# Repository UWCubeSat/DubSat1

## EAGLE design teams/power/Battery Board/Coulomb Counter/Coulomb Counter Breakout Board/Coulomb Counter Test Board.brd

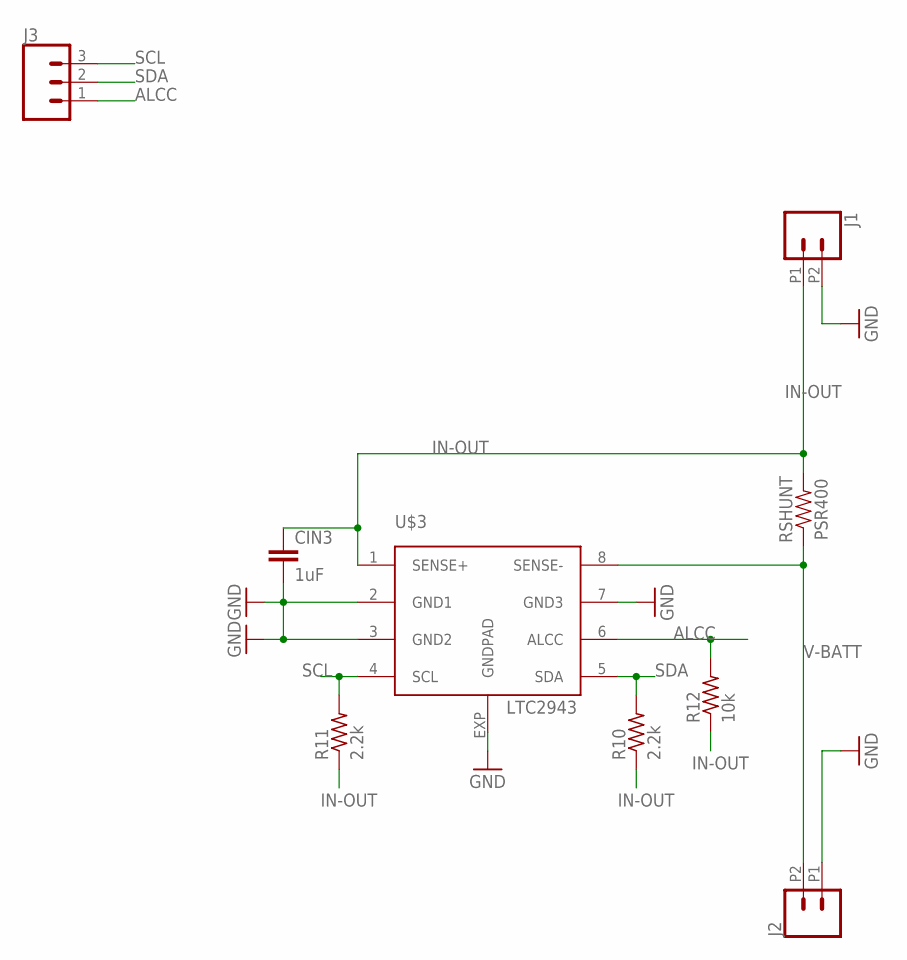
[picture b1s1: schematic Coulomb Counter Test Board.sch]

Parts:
CIN3: 1uF; 0402-CAP
J1, J2: CONN_022.54MM_SCREWTERM; 1X02_2.54_SCREWTERM
J3: CONN_03; 1X03
R10, R11: 2.2k; R0805
R12: 10k; R0805
RSHUNT: PSR400
U$3: LTC2943; DFN8(3X3)LT

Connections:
ALCC: J3.1, R12.2, U$3.6 (ALCC)
GND: CIN3.2, J1.P2 (2), J2.P1 (1), U$3.2 (GND1), U$3.3 (GND2), U$3.7 (GND3), U$3.EXP (GNDPAD)
IN-OUT: CIN3.1, J1.P1 (1), R10.1, R11.1, R12.1, RSHUNT.P$2 (2), U$3.1 (SENSE+)
SCL: J3.3, R11.2, U$3.4 (SCL)
SDA: J3.2, R10.2, U$3.5 (SDA)
V-BATT: J2.P2 (2), RSHUNT.P$1 (1), U$3.8 (SENSE-)

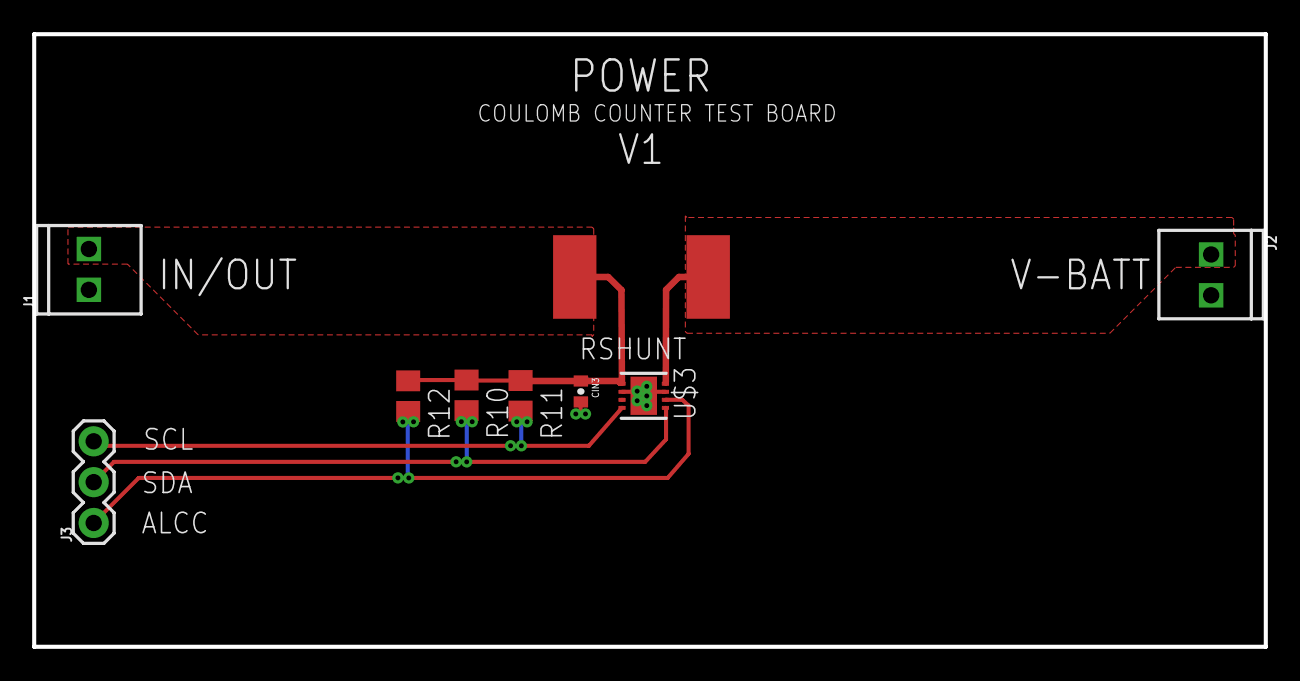
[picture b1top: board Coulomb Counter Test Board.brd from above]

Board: 2 copper layers, 76.6 x 38.1 mm, 9 parts (0 on the bottom side), 6 nets.

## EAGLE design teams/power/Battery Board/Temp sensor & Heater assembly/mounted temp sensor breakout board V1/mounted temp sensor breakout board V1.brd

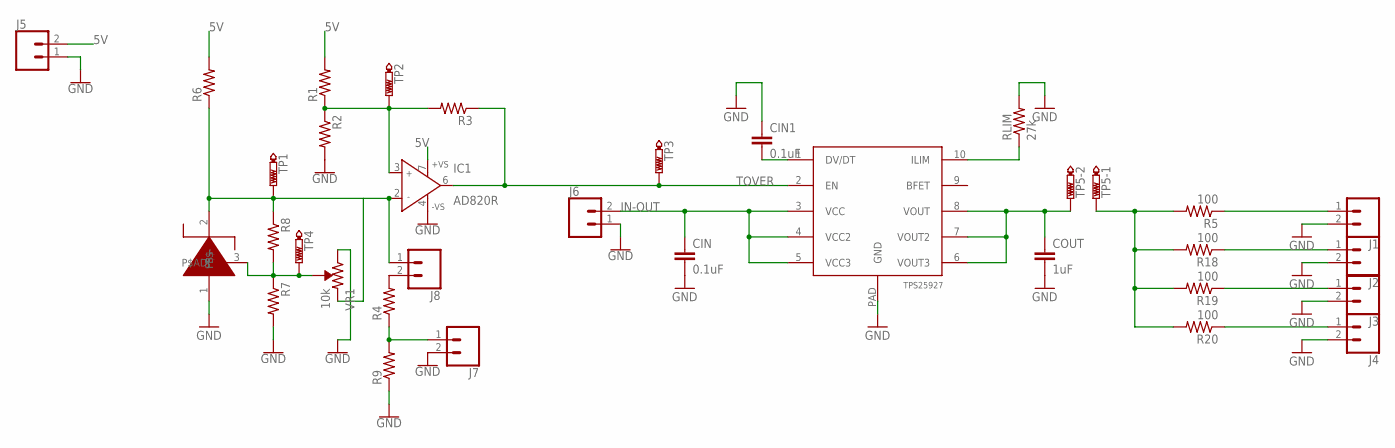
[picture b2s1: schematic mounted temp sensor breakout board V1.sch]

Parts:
CIN, CIN1: 0.1uF; C0805
COUT: 1uF; C0805
IC1: AD820R; SO8
J1, J2, J3, J4, J5, J6, J7, J8: CONN_02; 1X02
R1, R2, R3, R4, R6, R7, R8, R9: R-US_R0805; R0805
R5, R18, R19, R20: 100; R0805
RLIM: 27k; R0805
TP1, TP2, TP3, TP4: PTR1PAD1-13Y; P1-13Y
TP5: PTR2; P2-38-17
U$1: LM135Z; TO-92-3
U$5: TPS252927; VSON10
VR1: 10k; TRIMPOT-SMD-TC33X

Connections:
5V: IC1.7 (+VS), J5.2, R1.2, R6.2
GND: CIN.2, CIN1.1, COUT.2, IC1.4 (-VS), J1.2, J2.2, J3.2, J4.2, J5.1, J6.1, J7.2, R2.2, R7.2, R9.1, RLIM.2, U$1.1 (P$-), U$5.PAD (GND), VR1.1 (CW)
HEATER1: J3.1, R19.1
IN-OUT: CIN.1, J6.2, U$5.3 (VCC), U$5.4 (VCC2), U$5.5 (VCC3)
unnamed: J1.1, R5.1
unnamed: IC1.3 (IN+), R1.1, R2.1, R3.2, TP2.TP
unnamed: IC1.2 (IN-), J8.1, R6.1, R8.1, TP1.TP, U$1.2 (P$+), VR1.3 (CCW)
unnamed: R7.1, R8.2, TP4.TP, U$1.3 (P$ADJ), VR1.2 (WIPER)
unnamed: J2.1, R18.1
unnamed: J4.1, R20.1
unnamed: J7.1, R4.1, R9.2
unnamed: CIN1.2, U$5.1 (DV/DT)
unnamed: R5.2, R18.2, R19.2, R20.2, TP5.TP-1
unnamed: RLIM.1, U$5.10 (ILIM)
unnamed: J8.2, R4.2
unnamed: COUT.1, TP5.TP-2, U$5.6 (VOUT3), U$5.7 (VOUT2), U$5.8 (VOUT)
TOVER: IC1.6 (OUT), R3.1, TP3.TP, U$5.2 (EN)

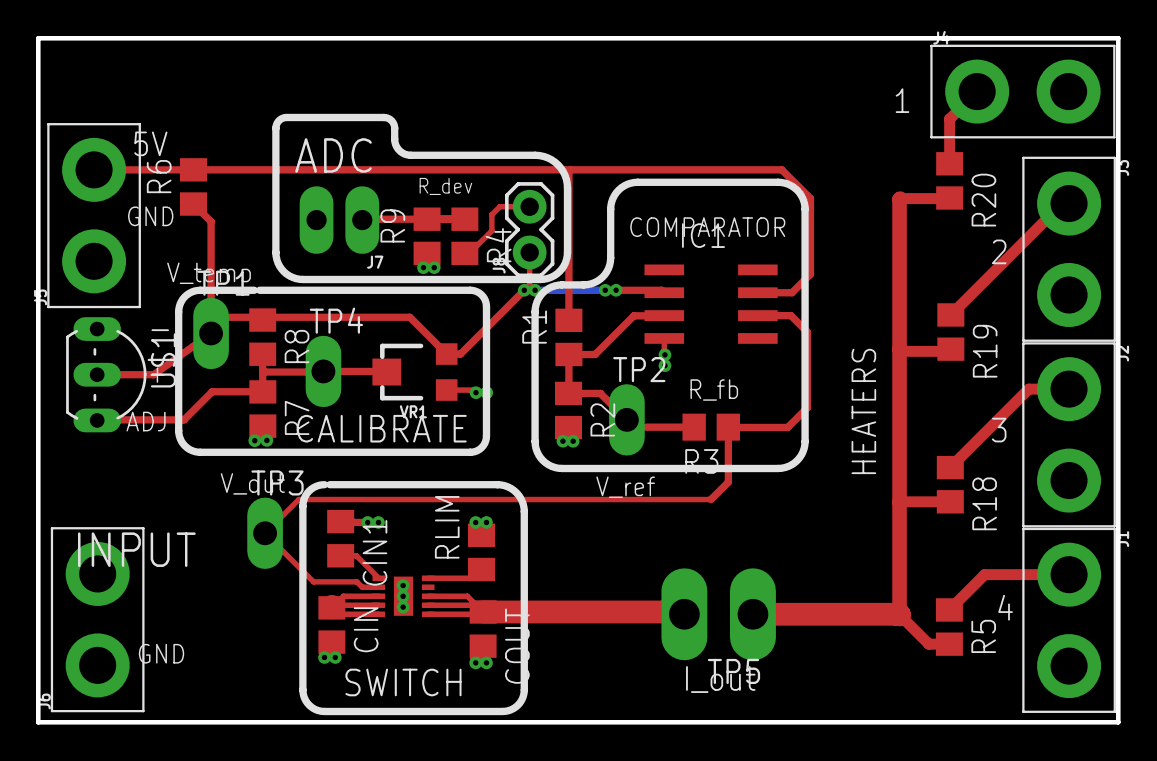
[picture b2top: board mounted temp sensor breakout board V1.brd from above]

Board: 2 copper layers, 60.0 x 38.0 mm, 33 parts (0 on the bottom side), 17 nets.

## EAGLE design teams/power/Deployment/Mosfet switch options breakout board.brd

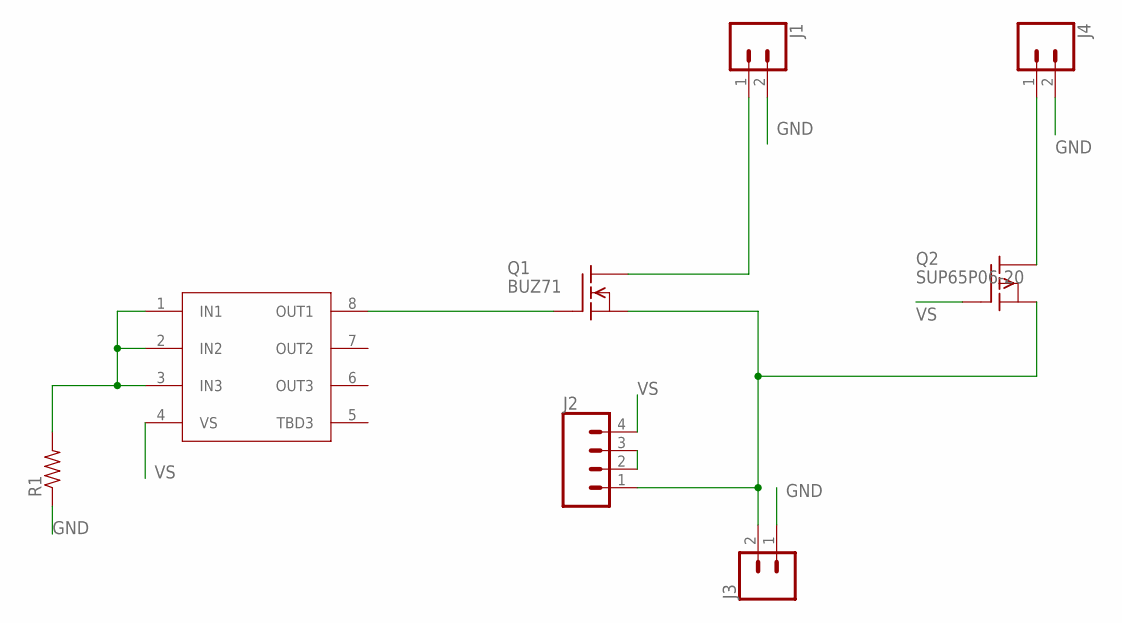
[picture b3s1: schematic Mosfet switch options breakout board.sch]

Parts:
J1, J3, J4: CONN_02; 1X02
J2: CONN_04; 1X04
Q1: BUZ71; TO220
Q2: SUP65P06-20; TO220
R1: RESISTOR0805; 0805
U$1: (TEMP)MOSFET_DRIVER; TSSOP-8

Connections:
GND: J1.2, J3.1, J4.2, R1.1
unnamed: Q1.1 (G), U$1.8 (OUT1)
unnamed: R1.2, U$1.1 (IN1), U$1.2 (IN2), U$1.3 (IN3)
unnamed: J4.1, Q2.2 (D)
unnamed: J1.1, Q1.2 (D)
unnamed: J2.2, J2.3
VBATT: J2.1, J3.2, Q1.3 (S), Q2.3 (S)
VS: J2.4, Q2.1 (G), U$1.4 (VS)

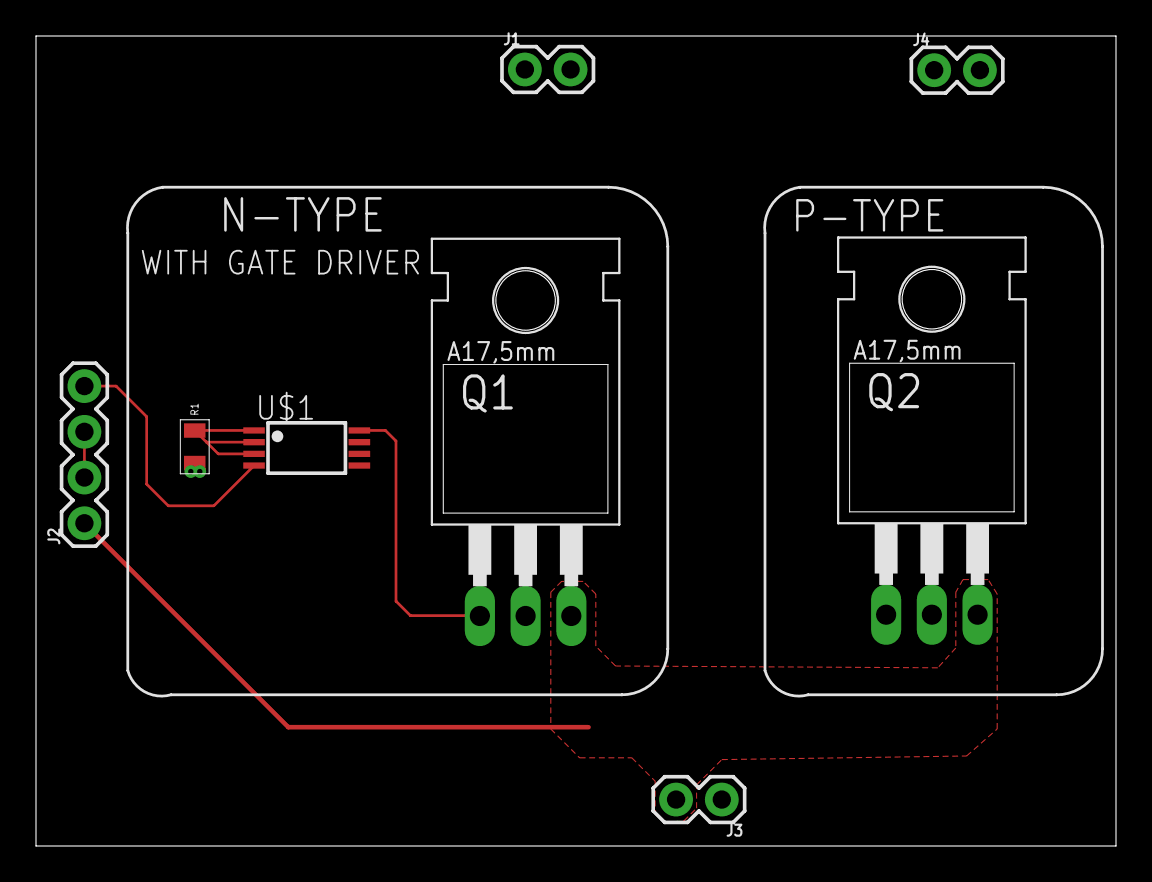
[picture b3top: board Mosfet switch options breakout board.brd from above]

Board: 2 copper layers, 60.0 x 45.0 mm, 8 parts (0 on the bottom side), 8 nets.

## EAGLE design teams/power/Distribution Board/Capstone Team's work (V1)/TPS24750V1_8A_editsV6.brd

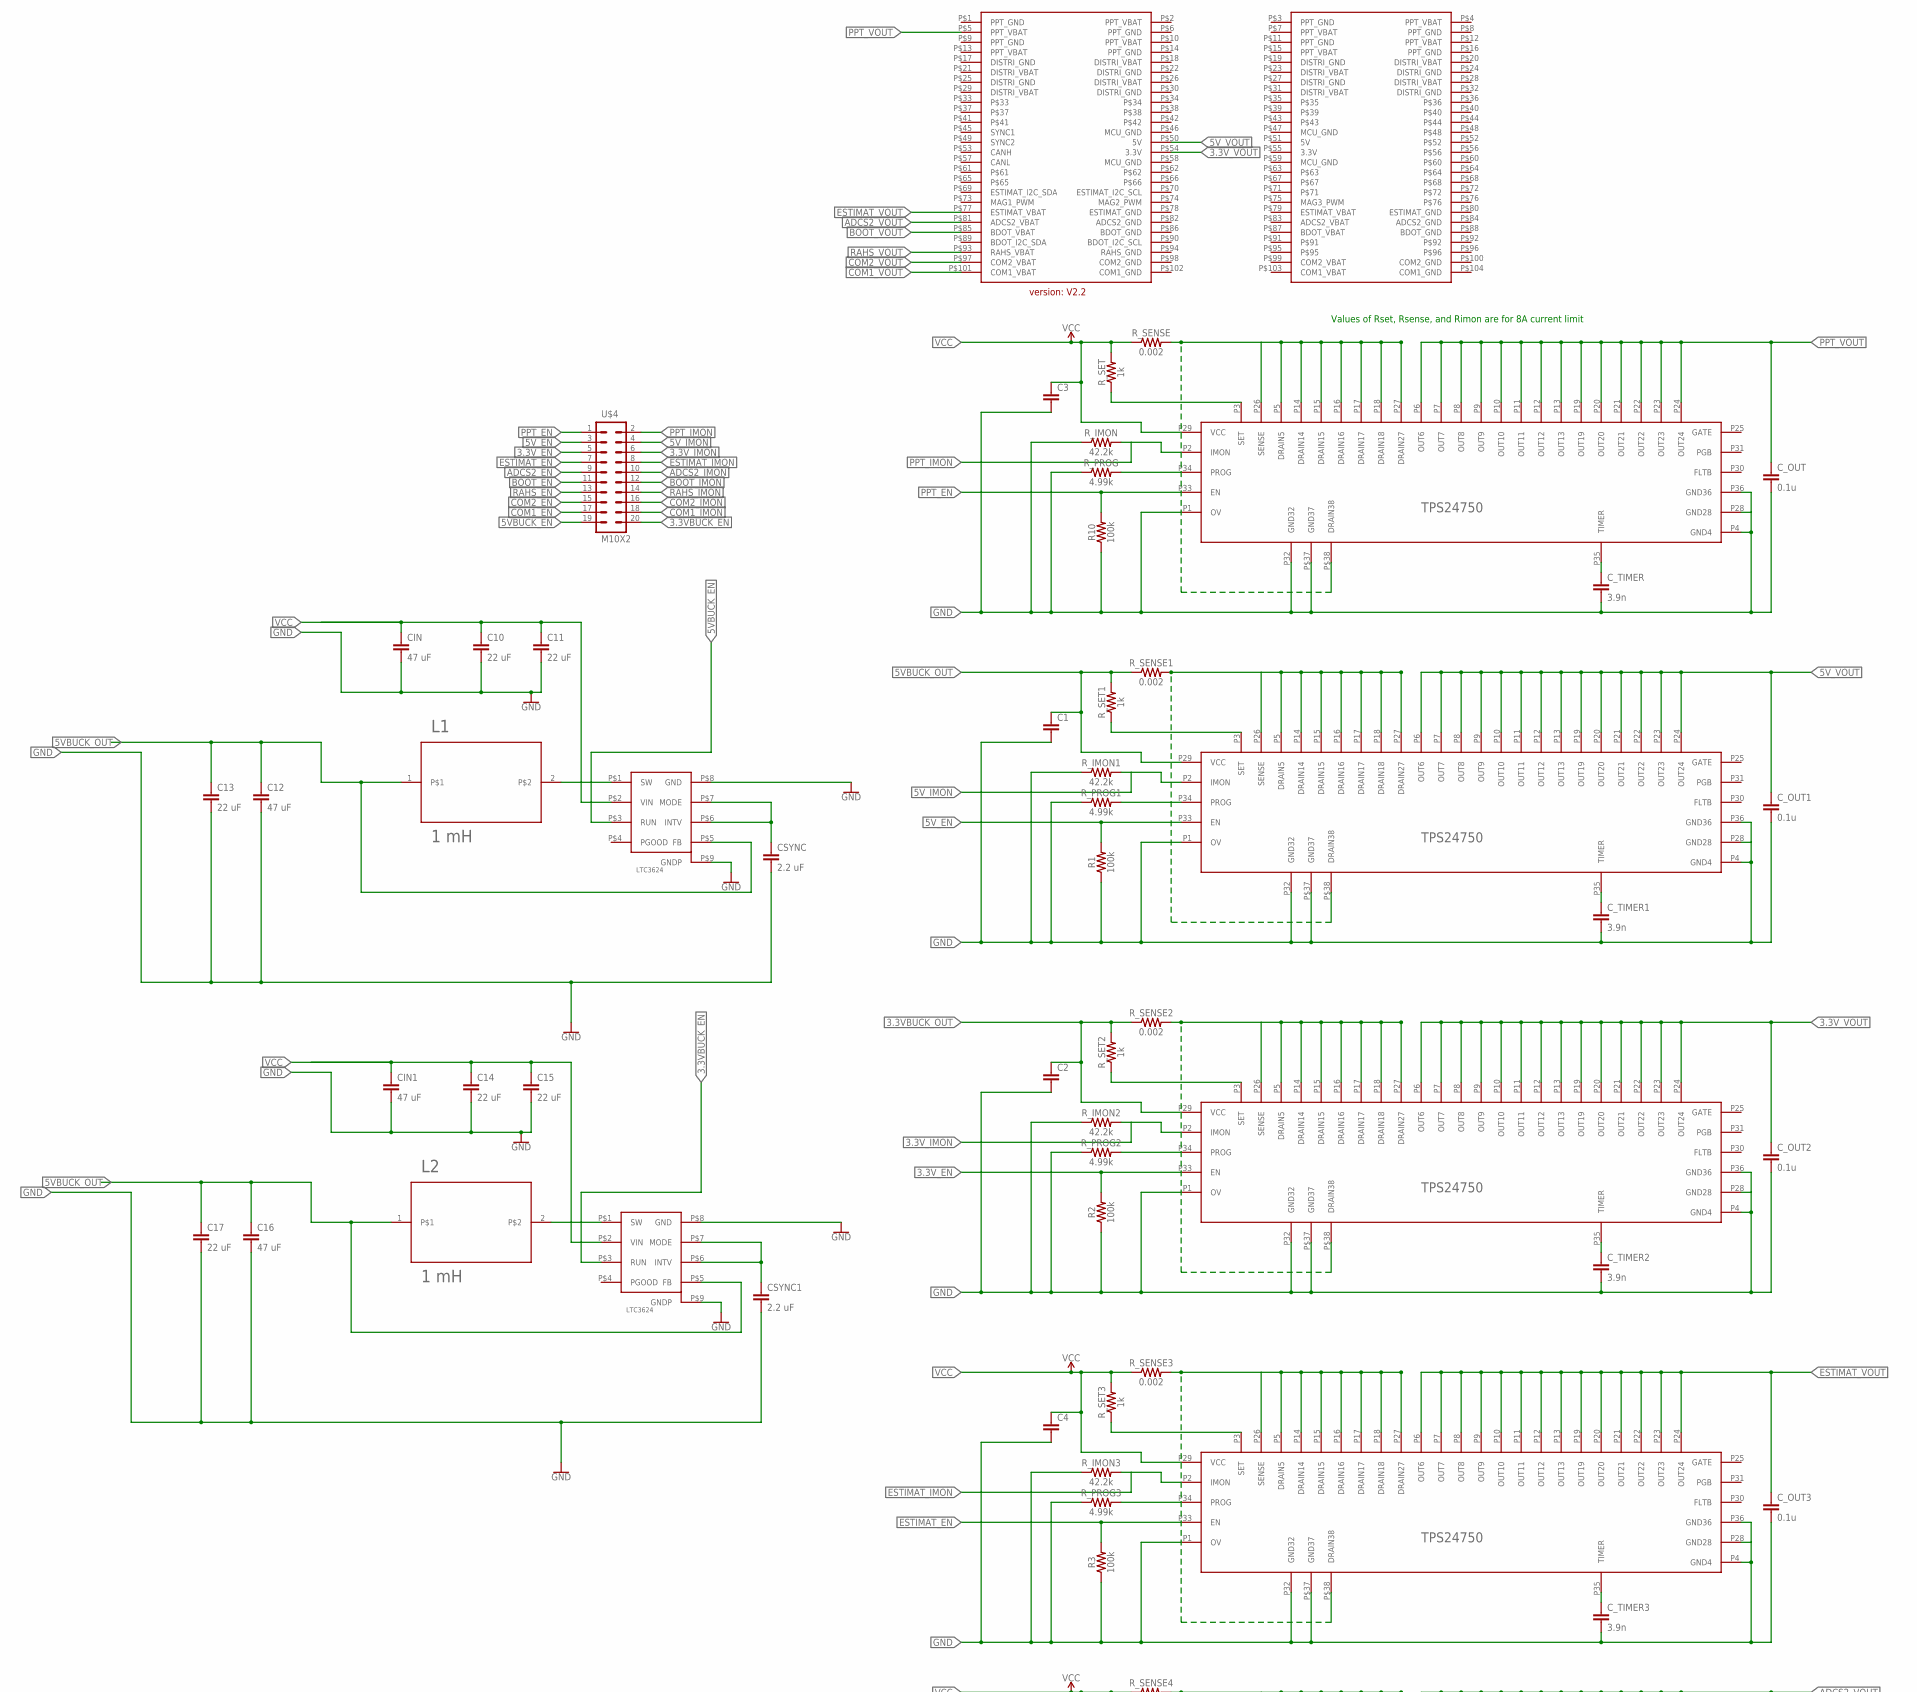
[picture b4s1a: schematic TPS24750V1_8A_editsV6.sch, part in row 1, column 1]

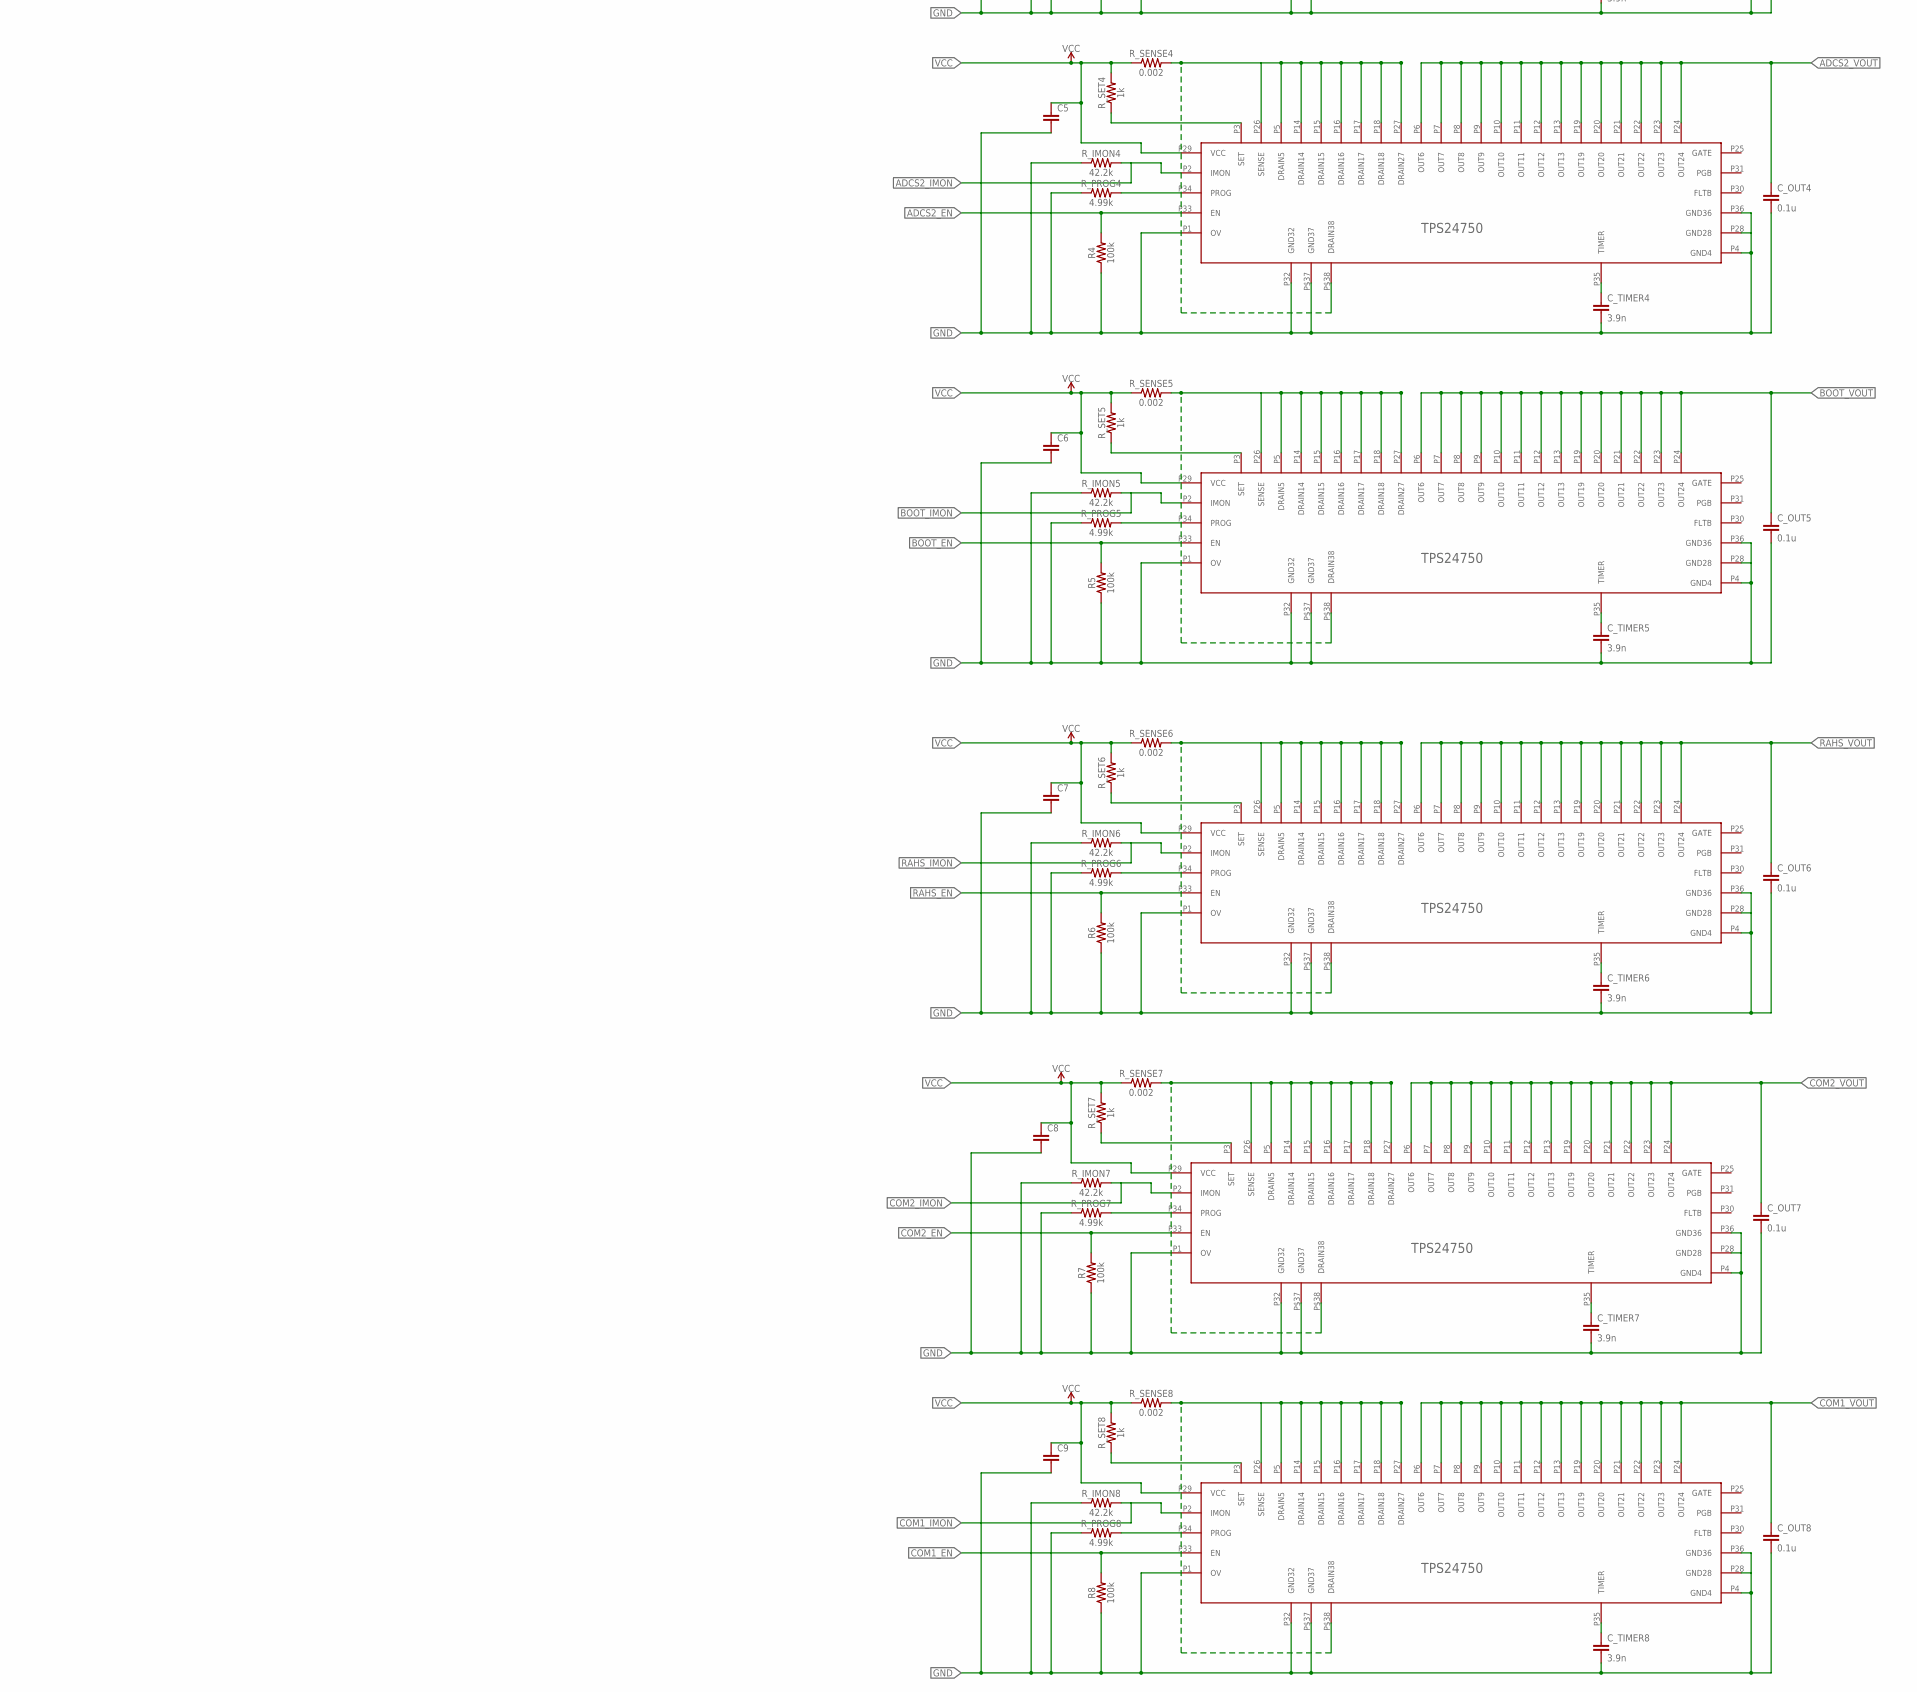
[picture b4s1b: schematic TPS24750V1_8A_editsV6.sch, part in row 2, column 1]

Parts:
C1, C2, C3, C4, C5, C6, C7, C8, C9: GEN_CAP_0805SMD; 0805
C10, C11, C13, C14, C15, C17: 22 uF; 1206
C12, C16: 47 uF; 1206
CIN, CIN1: 47 uF; 1206
CSYNC, CSYNC1: 2.2 uF; 0805
C_OUT, C_OUT1, C_OUT2, C_OUT3, C_OUT4, C_OUT5, C_OUT6, C_OUT7, C_OUT8: 0.1u; 0805
C_TIMER, C_TIMER1, C_TIMER2, C_TIMER3, C_TIMER4, C_TIMER5, C_TIMER6, C_TIMER7, C_TIMER8: 3.9n; 0805
L1, L2: 1 mH; COILCRAFT
R1, R2, R3, R4, R5, R6, R7, R8, R10: 100k; 0805
R_IMON, R_IMON1, R_IMON2, R_IMON3, R_IMON4, R_IMON5, R_IMON6, R_IMON7, R_IMON8: 42.2k; 0805
R_PROG, R_PROG1, R_PROG2, R_PROG3, R_PROG4, R_PROG5, R_PROG6, R_PROG7, R_PROG8: 4.99k; 0805
R_SENSE, R_SENSE1, R_SENSE2, R_SENSE3, R_SENSE4, R_SENSE5, R_SENSE6, R_SENSE7, R_SENSE8: 0.002; 2010
R_SET, R_SET1, R_SET2, R_SET3, R_SET4, R_SET5, R_SET6, R_SET7, R_SET8: 1k; 0805
U$1, U$5, U$6, U$7, U$8, U$9, U$10, U$11, U$12: TI_SWITCH_TPS24750; QFN-36
U$2: 2X26_CONNECTOR_(V2.2); 4X26_CONNECTOR_(V2.2)
U$4: M10X2; 2X10
U$13, U$14: LINEAR_BUCK_LTC3624; 8-LFCSP

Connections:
3.3VBUCK_EN: U$4.20, U$14.P$3 (RUN)
3.3VBUCK_OUT: C2.1, C16.1, C17.1, L2.1, R_SENSE2.1, R_SET2.2, U$6.P29 (VCC), U$14.P$5 (FB)
3.3V_EN: R2.2, U$4.5, U$6.P33 (EN)
3.3V_IMON: R_IMON2.2, U$4.6, U$6.P2 (IMON)
3.3V_VOUT: C_OUT2.1, U$2.P$54 (3.3V), U$6.P6 (OUT6), U$6.P7 (OUT7), U$6.P8 (OUT8), U$6.P9 (OUT9), U$6.P10 (OUT10), U$6.P11 (OUT11), U$6.P12 (OUT12), U$6.P13 (OUT13), U$6.P19 (OUT19), U$6.P20 (OUT20), U$6.P21 (OUT21), U$6.P22 (OUT22), U$6.P23 (OUT23), U$6.P24 (OUT24)
5VBUCK_EN: U$4.19, U$13.P$3 (RUN)
5VBUCK_OUT: C1.1, C12.1, C13.1, L1.1, R_SENSE1.1, R_SET1.2, U$5.P29 (VCC), U$13.P$5 (FB)
5V_EN: R1.2, U$4.3, U$5.P33 (EN)
5V_IMON: R_IMON1.2, U$4.4, U$5.P2 (IMON)
5V_VOUT: C_OUT1.1, U$2.P$50 (5V), U$5.P6 (OUT6), U$5.P7 (OUT7), U$5.P8 (OUT8), U$5.P9 (OUT9), U$5.P10 (OUT10), U$5.P11 (OUT11), U$5.P12 (OUT12), U$5.P13 (OUT13), U$5.P19 (OUT19), U$5.P20 (OUT20), U$5.P21 (OUT21), U$5.P22 (OUT22), U$5.P23 (OUT23), U$5.P24 (OUT24)
ADCS2_EN: R4.2, U$4.9, U$8.P33 (EN)
ADCS2_IMON: R_IMON4.2, U$4.10, U$8.P2 (IMON)
ADCS2_VOUT: C_OUT4.1, U$2.P$81 (ADCS2_VBAT), U$8.P6 (OUT6), U$8.P7 (OUT7), U$8.P8 (OUT8), U$8.P9 (OUT9), U$8.P10 (OUT10), U$8.P11 (OUT11), U$8.P12 (OUT12), U$8.P13 (OUT13), U$8.P19 (OUT19), U$8.P20 (OUT20), U$8.P21 (OUT21), U$8.P22 (OUT22), U$8.P23 (OUT23), U$8.P24 (OUT24)
BOOT_EN: R5.2, U$9.P33 (EN)
BOOT_IMON: R_IMON5.2, U$9.P2 (IMON)
BOOT_VOUT: C_OUT5.1, U$2.P$85 (BDOT_VBAT), U$9.P6 (OUT6), U$9.P7 (OUT7), U$9.P8 (OUT8), U$9.P9 (OUT9), U$9.P10 (OUT10), U$9.P11 (OUT11), U$9.P12 (OUT12), U$9.P13 (OUT13), U$9.P19 (OUT19), U$9.P20 (OUT20), U$9.P21 (OUT21), U$9.P22 (OUT22), U$9.P23 (OUT23), U$9.P24 (OUT24)
COM1_EN: R8.2, U$4.17, U$12.P33 (EN)
COM1_IMON: R_IMON8.2, U$12.P2 (IMON)
COM1_VOUT: C_OUT8.1, U$2.P$101 (COM1_VBAT), U$12.P6 (OUT6), U$12.P7 (OUT7), U$12.P8 (OUT8), U$12.P9 (OUT9), U$12.P10 (OUT10), U$12.P11 (OUT11), U$12.P12 (OUT12), U$12.P13 (OUT13), U$12.P19 (OUT19), U$12.P20 (OUT20), U$12.P21 (OUT21), U$12.P22 (OUT22), U$12.P23 (OUT23), U$12.P24 (OUT24)
COM2_EN: R7.2, U$11.P33 (EN)
COM2_IMON: R_IMON7.2, U$4.16, U$11.P2 (IMON)
COM2_VOUT: C_OUT7.1, U$2.P$97 (COM2_VBAT), U$11.P6 (OUT6), U$11.P7 (OUT7), U$11.P8 (OUT8), U$11.P9 (OUT9), U$11.P10 (OUT10), U$11.P11 (OUT11), U$11.P12 (OUT12), U$11.P13 (OUT13), U$11.P19 (OUT19), U$11.P20 (OUT20), U$11.P21 (OUT21), U$11.P22 (OUT22), U$11.P23 (OUT23), U$11.P24 (OUT24)
DRAIN: R_SENSE.2, U$1.P5 (DRAIN5), U$1.P14 (DRAIN14), U$1.P15 (DRAIN15), U$1.P16 (DRAIN16), U$1.P17 (DRAIN17), U$1.P18 (DRAIN18), U$1.P26 (SENSE), U$1.P27 (DRAIN27), U$1.P$38 (DRAIN38)
DRAIN1: R_SENSE1.2, U$5.P5 (DRAIN5), U$5.P14 (DRAIN14), U$5.P15 (DRAIN15), U$5.P16 (DRAIN16), U$5.P17 (DRAIN17), U$5.P18 (DRAIN18), U$5.P26 (SENSE), U$5.P27 (DRAIN27), U$5.P$38 (DRAIN38)
DRAIN2: R_SENSE2.2, U$6.P5 (DRAIN5), U$6.P14 (DRAIN14), U$6.P15 (DRAIN15), U$6.P16 (DRAIN16), U$6.P17 (DRAIN17), U$6.P18 (DRAIN18), U$6.P26 (SENSE), U$6.P27 (DRAIN27), U$6.P$38 (DRAIN38)
DRAIN3: R_SENSE3.2, U$7.P5 (DRAIN5), U$7.P14 (DRAIN14), U$7.P15 (DRAIN15), U$7.P16 (DRAIN16), U$7.P17 (DRAIN17), U$7.P18 (DRAIN18), U$7.P26 (SENSE), U$7.P27 (DRAIN27), U$7.P$38 (DRAIN38)
DRAIN4: R_SENSE4.2, U$8.P5 (DRAIN5), U$8.P14 (DRAIN14), U$8.P15 (DRAIN15), U$8.P16 (DRAIN16), U$8.P17 (DRAIN17), U$8.P18 (DRAIN18), U$8.P26 (SENSE), U$8.P27 (DRAIN27), U$8.P$38 (DRAIN38)
DRAIN5: R_SENSE5.2, U$9.P5 (DRAIN5), U$9.P14 (DRAIN14), U$9.P15 (DRAIN15), U$9.P16 (DRAIN16), U$9.P17 (DRAIN17), U$9.P18 (DRAIN18), U$9.P26 (SENSE), U$9.P27 (DRAIN27), U$9.P$38 (DRAIN38)
DRAIN6: R_SENSE6.2, U$10.P5 (DRAIN5), U$10.P14 (DRAIN14), U$10.P15 (DRAIN15), U$10.P16 (DRAIN16), U$10.P17 (DRAIN17), U$10.P18 (DRAIN18), U$10.P26 (SENSE), U$10.P27 (DRAIN27), U$10.P$38 (DRAIN38)
DRAIN7: R_SENSE7.2, U$11.P5 (DRAIN5), U$11.P14 (DRAIN14), U$11.P15 (DRAIN15), U$11.P16 (DRAIN16), U$11.P17 (DRAIN17), U$11.P18 (DRAIN18), U$11.P26 (SENSE), U$11.P27 (DRAIN27), U$11.P$38 (DRAIN38)
DRAIN8: R_SENSE8.2, U$12.P5 (DRAIN5), U$12.P14 (DRAIN14), U$12.P15 (DRAIN15), U$12.P16 (DRAIN16), U$12.P17 (DRAIN17), U$12.P18 (DRAIN18), U$12.P26 (SENSE), U$12.P27 (DRAIN27), U$12.P$38 (DRAIN38)
ESTIMAT_EN: R3.2, U$4.7, U$7.P33 (EN)
ESTIMAT_IMON: R_IMON3.2, U$4.8, U$7.P2 (IMON)
ESTIMAT_VOUT: C_OUT3.1, U$2.P$77 (ESTIMAT_VBAT), U$7.P6 (OUT6), U$7.P7 (OUT7), U$7.P8 (OUT8), U$7.P9 (OUT9), U$7.P10 (OUT10), U$7.P11 (OUT11), U$7.P12 (OUT12), U$7.P13 (OUT13), U$7.P19 (OUT19), U$7.P20 (OUT20), U$7.P21 (OUT21), U$7.P22 (OUT22), U$7.P23 (OUT23), U$7.P24 (OUT24)
GND: C1.2, C2.2, C3.2, C4.2, C5.2, C6.2, C7.2, C8.2, C9.2, C10.2, C11.2, C12.2, C13.2, C14.2, C15.2, C16.2, C17.2, CIN.2, CIN1.2, CSYNC.2, CSYNC1.2, C_OUT.2, C_OUT1.2, C_OUT2.2, C_OUT3.2, C_OUT4.2, C_OUT5.2, C_OUT6.2, C_OUT7.2, C_OUT8.2, C_TIMER.2, C_TIMER1.2, C_TIMER2.2, C_TIMER3.2, C_TIMER4.2, C_TIMER5.2, C_TIMER6.2, C_TIMER7.2, C_TIMER8.2, R1.1, R2.1, R3.1, R4.1, R5.1, R6.1, R7.1, R8.1, R10.1, R_IMON.1, R_IMON1.1, R_IMON2.1, R_IMON3.1, R_IMON4.1, R_IMON5.1, R_IMON6.1, R_IMON7.1, R_IMON8.1, R_PROG.1, R_PROG1.1, R_PROG2.1, R_PROG3.1, R_PROG4.1, R_PROG5.1, R_PROG6.1, R_PROG7.1, R_PROG8.1, U$1.P1 (OV), U$1.P4 (GND4), U$1.P28 (GND28), U$1.P32 (GND32), U$1.P36 (GND36), U$1.P$37 (GND37), U$5.P1 (OV), U$5.P4 (GND4), U$5.P28 (GND28), U$5.P32 (GND32), U$5.P36 (GND36), U$5.P$37 (GND37), U$6.P1 (OV), U$6.P4 (GND4), U$6.P28 (GND28), U$6.P32 (GND32), U$6.P36 (GND36), U$6.P$37 (GND37), U$7.P1 (OV), U$7.P4 (GND4), U$7.P28 (GND28), U$7.P32 (GND32), U$7.P36 (GND36), U$7.P$37 (GND37), U$8.P1 (OV), U$8.P4 (GND4), U$8.P28 (GND28), U$8.P32 (GND32), U$8.P36 (GND36), U$8.P$37 (GND37), U$9.P1 (OV), U$9.P4 (GND4), U$9.P28 (GND28), U$9.P32 (GND32), U$9.P36 (GND36), U$9.P$37 (GND37), U$10.P1 (OV), U$10.P4 (GND4), U$10.P28 (GND28), U$10.P32 (GND32), U$10.P36 (GND36), U$10.P$37 (GND37), U$11.P1 (OV), U$11.P4 (GND4), U$11.P28 (GND28), U$11.P32 (GND32), U$11.P36 (GND36), U$11.P$37 (GND37), U$12.P1 (OV), U$12.P4 (GND4), U$12.P28 (GND28), U$12.P32 (GND32), U$12.P36 (GND36), U$12.P$37 (GND37), U$13.P$8 (GND), U$13.P$9 (GNDP), U$14.P$8 (GND), U$14.P$9 (GNDP)
INPUT6_EN: U$4.11
INPUT6_IMON: U$4.12
INPUT8_EN: U$4.15
INPUT9_IMON: U$4.18
MODE: CSYNC.1, U$13.P$6 (INTV), U$13.P$7 (MODE)
MODE1: CSYNC1.1, U$14.P$6 (INTV), U$14.P$7 (MODE)
PPT_EN: R10.2, U$1.P33 (EN), U$4.1
PPT_IMON: R_IMON.2, U$1.P2 (IMON), U$4.2
PPT_VOUT: C_OUT.1, U$1.P6 (OUT6), U$1.P7 (OUT7), U$1.P8 (OUT8), U$1.P9 (OUT9), U$1.P10 (OUT10), U$1.P11 (OUT11), U$1.P12 (OUT12), U$1.P13 (OUT13), U$1.P19 (OUT19), U$1.P20 (OUT20), U$1.P21 (OUT21), U$1.P22 (OUT22), U$1.P23 (OUT23), U$1.P24 (OUT24), U$2.P$5 (PPT_VBAT)
PROG: R_PROG.2, U$1.P34 (PROG)
PROG1: R_PROG1.2, U$5.P34 (PROG)
PROG2: R_PROG2.2, U$6.P34 (PROG)
PROG3: R_PROG3.2, U$7.P34 (PROG)
PROG4: R_PROG4.2, U$8.P34 (PROG)
PROG5: R_PROG5.2, U$9.P34 (PROG)
PROG6: R_PROG6.2, U$10.P34 (PROG)
PROG7: R_PROG7.2, U$11.P34 (PROG)
PROG8: R_PROG8.2, U$12.P34 (PROG)
RAHS_EN: R6.2, U$4.13, U$10.P33 (EN)
RAHS_IMON: R_IMON6.2, U$4.14, U$10.P2 (IMON)
RAHS_VOUT: C_OUT6.1, U$2.P$93 (RAHS_VBAT), U$10.P6 (OUT6), U$10.P7 (OUT7), U$10.P8 (OUT8), U$10.P9 (OUT9), U$10.P10 (OUT10), U$10.P11 (OUT11), U$10.P12 (OUT12), U$10.P13 (OUT13), U$10.P19 (OUT19), U$10.P20 (OUT20), U$10.P21 (OUT21), U$10.P22 (OUT22), U$10.P23 (OUT23), U$10.P24 (OUT24)
SET: R_SET.1, U$1.P3 (SET)
SET1: R_SET1.1, U$5.P3 (SET)
SET2: R_SET2.1, U$6.P3 (SET)
SET3: R_SET3.1, U$7.P3 (SET)
SET4: R_SET4.1, U$8.P3 (SET)
SET5: R_SET5.1, U$9.P3 (SET)
SET6: R_SET6.1, U$10.P3 (SET)
SET7: R_SET7.1, U$11.P3 (SET)
SET8: R_SET8.1, U$12.P3 (SET)
SW: L1.2, U$13.P$1 (SW)
SW1: L2.2, U$14.P$1 (SW)
TIMER: C_TIMER.1, U$1.P35 (TIMER)
TIMER1: C_TIMER1.1, U$5.P35 (TIMER)
TIMER2: C_TIMER2.1, U$6.P35 (TIMER)
TIMER3: C_TIMER3.1, U$7.P35 (TIMER)
TIMER4: C_TIMER4.1, U$8.P35 (TIMER)
TIMER5: C_TIMER5.1, U$9.P35 (TIMER)
TIMER6: C_TIMER6.1, U$10.P35 (TIMER)
TIMER7: C_TIMER7.1, U$11.P35 (TIMER)
TIMER8: C_TIMER8.1, U$12.P35 (TIMER)
VCC: C3.1, C4.1, C5.1, C6.1, C7.1, C8.1, C9.1, C10.1, C11.1, C14.1, C15.1, CIN.1, CIN1.1, R_SENSE.1, R_SENSE3.1, R_SENSE4.1, R_SENSE5.1, R_SENSE6.1, R_SENSE7.1, R_SENSE8.1, R_SET.2, R_SET3.2, R_SET4.2, R_SET5.2, R_SET6.2, R_SET7.2, R_SET8.2, U$1.P29 (VCC), U$7.P29 (VCC), U$8.P29 (VCC), U$9.P29 (VCC), U$10.P29 (VCC), U$11.P29 (VCC), U$12.P29 (VCC), U$13.P$2 (VIN), U$14.P$2 (VIN)

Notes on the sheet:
Values of Rset, Rsense, and Rimon are for 8A current limit

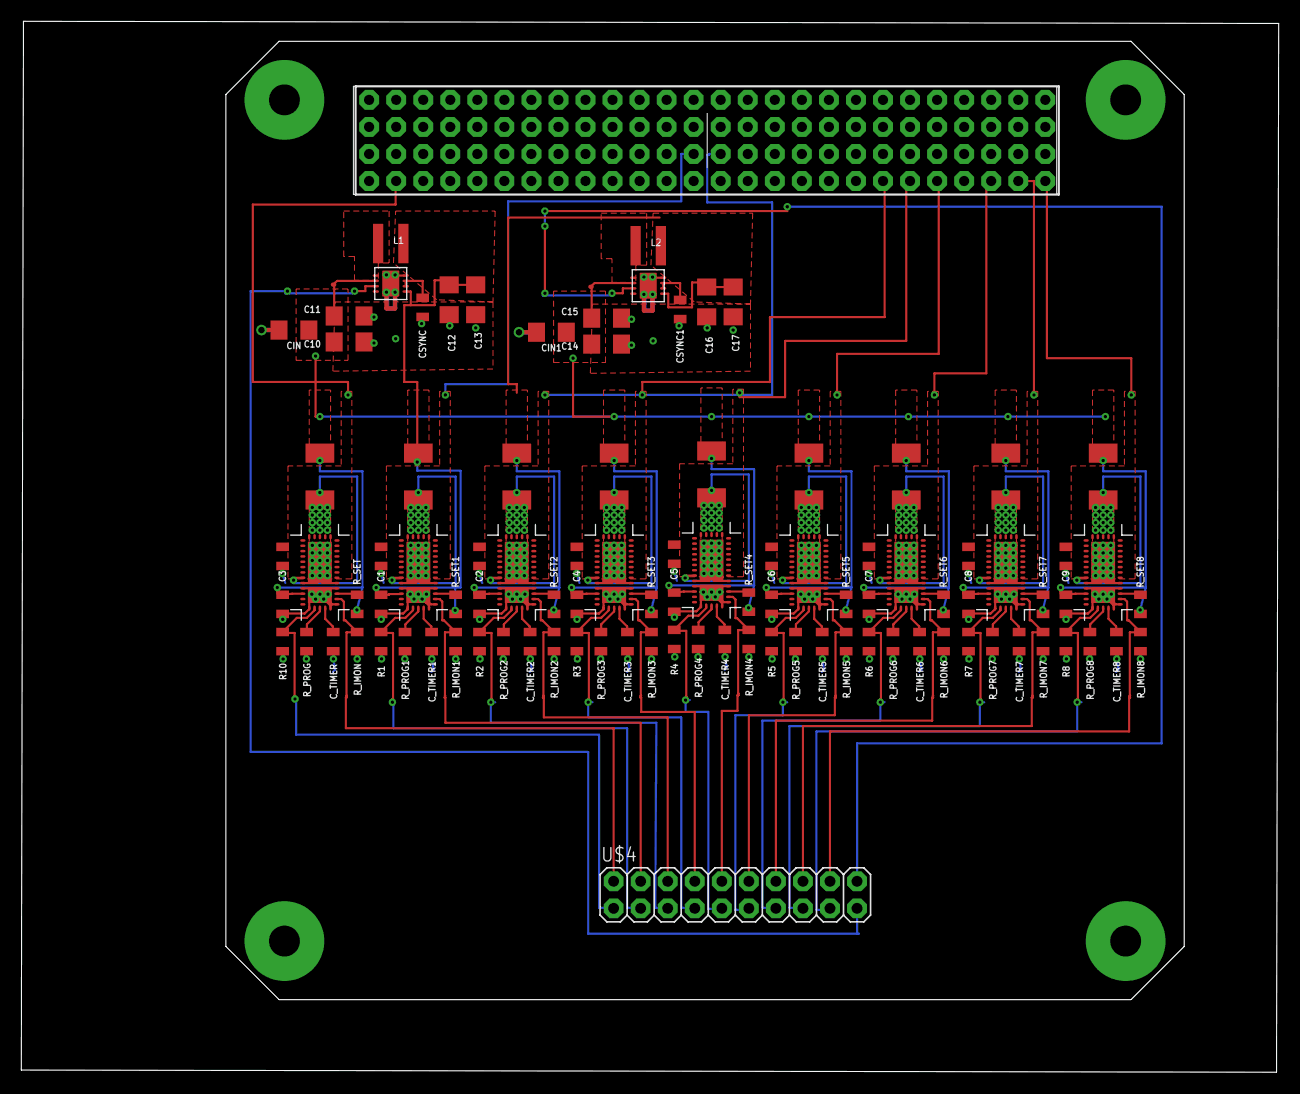
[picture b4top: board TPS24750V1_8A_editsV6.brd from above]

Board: 2 copper layers, 118.1 x 98.7 mm, 100 parts (0 on the bottom side), 73 nets.

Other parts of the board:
U$3: BOARD_TEMPLATE_(V2.1)

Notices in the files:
parts and their libraries:
SparkFun-Retired: Licensing: Creative Commons ShareAlike 4.0 International - https://creativecommons.org/licenses/by-sa/4.0
